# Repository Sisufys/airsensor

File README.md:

# airsensor
Air quality meter that uses SCD30 and SPS30 sensors from sensirion. WORK IN PROGRESS

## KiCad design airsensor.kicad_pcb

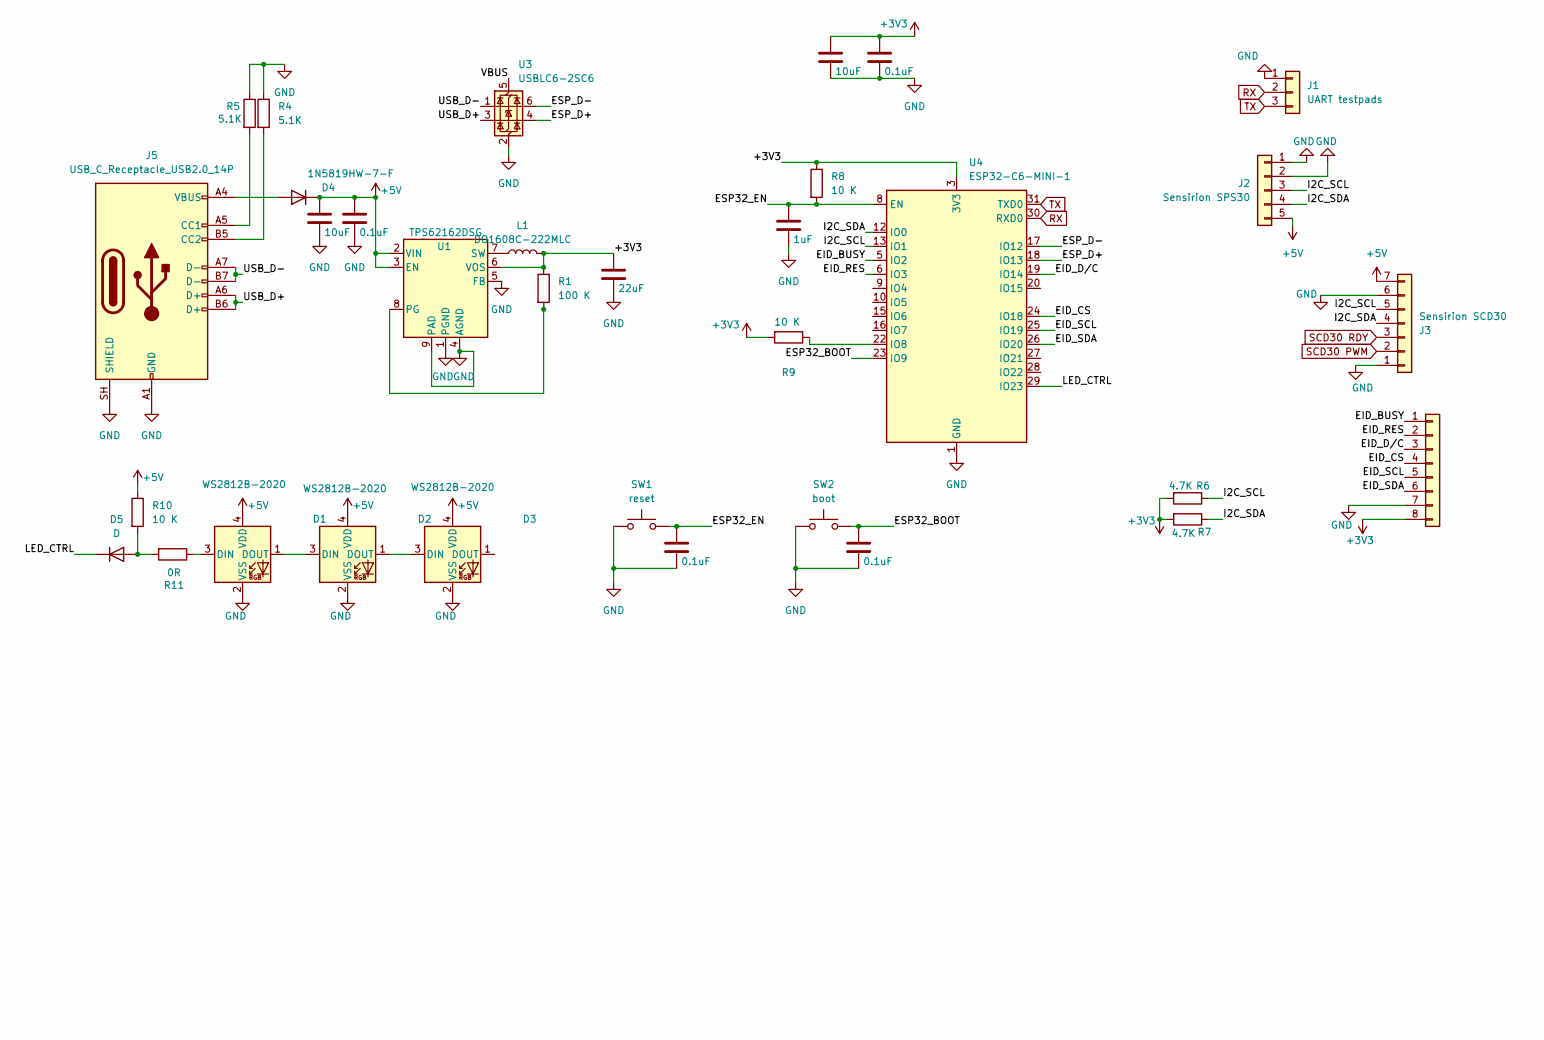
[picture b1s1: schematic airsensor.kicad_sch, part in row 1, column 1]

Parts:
C1, C6: 10uF; C_1206_3216Metric_Pad1.33x1.80mm_HandSolder
C2: 22uF; C_1812_4532Metric_Pad1.57x3.40mm_HandSolder
C4: 1uF; C_0805_2012Metric_Pad1.18x1.45mm_HandSolder
C5, C7, C8, C9: 0.1uF; C_1206_3216Metric_Pad1.33x1.80mm_HandSolder
D1, D2, D3: WS2812B-2020; LED_WS2812B-2020_PLCC4_2.0x2.0mm
D4: 1N5819HW-7-F; D_SOD-123
D5: D; D_DO-35_SOD27_P10.16mm_Horizontal
J1: UART testpads; PinHeader_1x03_P2.54mm_Vertical
J2: Sensirion SPS30; PinHeader_1x05_P2.54mm_Vertical
J3: Sensirion SCD30; PinSocket_1x07_P2.54mm_Vertical
J4: E-ink; PinHeader_1x08_P2.54mm_Vertical
J5: USB_C_Receptacle_USB2.0_14P; USB_C_Receptacle_GCT_USB4105-xx-A_16P_TopMnt_Horizontal
L1: DO1608C-222MLC; L_APV_ANR6045
R1: 100 K; C_0805_2012Metric_Pad1.18x1.45mm_HandSolder
R4, R5: 5.1K; R_0805_2012Metric
R6, R7: 4.7K; R_0805_2012Metric
R8, R9, R10: 10 K; R_0805_2012Metric
R11: 0R; SolderJumper-2_P1.3mm_Open_TrianglePad1.0x1.5mm
SW1: reset; SW_Push_1P1T_NO_E-Switch_TL3301NxxxxxG
SW2: boot; SW_Push_1P1T_NO_E-Switch_TL3301NxxxxxG
U1: TPS62162DSG; Texas_DSG0008A_WSON-8-1EP_2x2mm_P0.5mm_EP0.9x1.6mm_ThermalV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
U3: USBLC6-2SC6; SOT-23-6
U4: ESP32-C6-MINI-1

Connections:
+3V3: C2.1, C5.1, C6.1, J4.8, L1.2, R1.1, R6.2, R7.2, R8.1, R9.2, U1.6 (VOS), U4.3 (3V3)
+5V: C1.1, C8.1, D1.4 (VDD), D2.4 (VDD), D3.4 (VDD), D4.1 (K), J2.5, J3.7, R10.1, U1.2 (VIN), U1.3 (EN)
/EID_BUSY: J4.1, U4.5 (IO2)
/EID_CS: J4.4, U4.24 (IO18)
/EID_D/C: J4.3, U4.19 (IO14)
/EID_RES: J4.2, U4.6 (IO3)
/EID_SCL: J4.5, U4.25 (IO19)
/EID_SDA: J4.6, U4.26 (IO20)
/ESP32_BOOT: C7.1, SW2.2, U4.23 (IO9)
/ESP32_EN: C4.1, C9.1, R8.2, SW1.2, U4.8 (EN)
/ESP_D+: U3.4 (I/O2), U4.18 (IO13)
/ESP_D-: U3.6 (I/O1), U4.17 (IO12)
/I2C_SCL: J2.3, J3.5, R6.1, U4.13 (IO1)
/I2C_SDA: J2.4, J3.4, R7.1, U4.12 (IO0)
/LED_CTRL: D5.1 (K), U4.29 (IO23)
/USB_D+: J5.A6 (D+), J5.B6 (D+), U3.3 (I/O2)
/USB_D-: J5.A7 (D-), J5.B7 (D-), U3.1 (I/O1)
GND: C1.2, C2.2, C4.2, C5.2, C6.2, C7.2, C8.2, C9.2, D1.2 (VSS), D2.2 (VSS), D3.2 (VSS), J1.1, J2.1, J2.2, J3.1, J3.6, J4.7, J5.A1 (GND), J5.A12 (GND), J5.B1 (GND), J5.B12 (GND), J5.SH (SHIELD), R4.1, R5.1, SW1.1, SW2.1, U1.1 (PGND), U1.4 (AGND), U1.5 (FB), U1.9 (PAD), U3.2 (GND), U4.1 (GND), U4.2 (GND), U4.11 (GND), U4.14 (GND), U4.36 (GND), U4.37 (GND), U4.38 (GND), U4.39 (GND), U4.40 (GND), U4.41 (GND), U4.42 (GND), U4.43 (GND), U4.44 (GND), U4.45 (GND), U4.46 (GND), U4.47 (GND), U4.48 (GND), U4.49 (GND), U4.50 (GND), U4.51 (GND), U4.52 (GND), U4.53 (GND); also elsewhere on the board
unnamed: D1.3 (DIN), R11.1
unnamed: D1.1 (DOUT), D2.3 (DIN)
unnamed: D2.1 (DOUT), D3.3 (DIN)
unnamed: D5.2 (A), R10.2, R11.2
unnamed: J5.A5 (CC1), R5.2
unnamed: J5.B5 (CC2), R4.2
unnamed: R1.2, U1.8 (PG)
unnamed: L1.1, U1.7 (SW)
unnamed: R9.1, U4.22 (IO8)
RX: J1.2, U4.30 (RXD0)
SCD30 PWM: J3.2
SCD30 RDY: J3.3
TX: J1.3, U4.31 (TXD0)

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
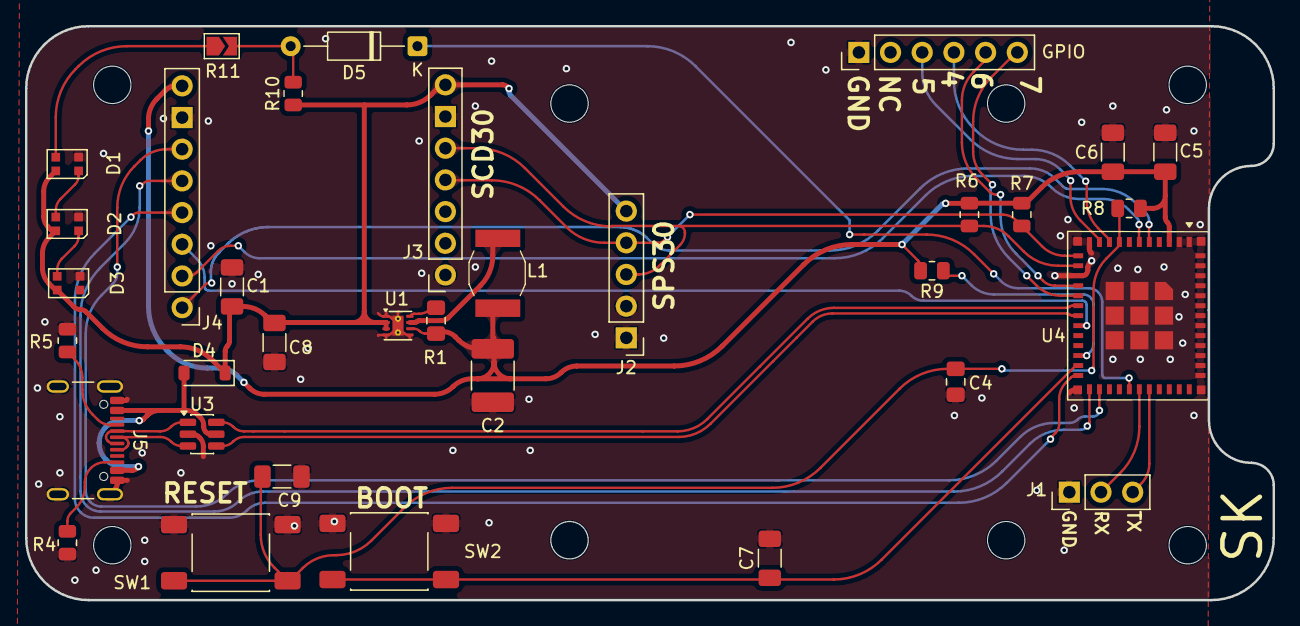
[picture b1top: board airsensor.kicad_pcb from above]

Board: 2 copper layers, 100.0 x 46.0 mm, 34 parts (0 on the bottom side), 30 nets.

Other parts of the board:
GPIO: PinHeader_1x06_P2.54mm_Vertical

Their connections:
GND: GPIO.1; also elsewhere on the board
